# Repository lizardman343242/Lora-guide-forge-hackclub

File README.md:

# Lora-guide-forge-hackclub

This project follows the stranded guide from forge connecting the RP2040 to the Lora module leading into a antenna 

Bom Table
---
| Id | Designator | Footprint | Quantity | Designation | Supplier and ref |
|----|------------|-----------|----------|--------------|-------------------|
| 1 | AE1 | PinSocket_1x01_P2.54mm_Vertical | 1 | Antenna | |
| 2 | C2, C3 | C_0402_1005Metric | 2 | 100nf | https://jlcpcb.com/partdetail/1877-CL05B104KO5NNNC/C1525|
| 3 | C4 | C_0402_1005Metric | 1 | 470nF | https://jlcpcb.com/partdetail/48344-CL05A474KP5NNNC/C47339|
| 4 | C5, C6 | C_0402_1005Metric | 2 | 47pF | https://jlcpcb.com/partdetail/1919-0402CG470J500NT/C1567|
| 5 | C7 | C_0402_1005Metric | 1 | 1nf | https://jlcpcb.com/partdetail/1875-0402B102K500NT/C1523|
| 6 | C8 | C_0402_1005Metric | 1 | 39pF | https://jlcpcb.com/partdetail/1915-0402CG390J500NT/C1563|
| 7 | C9, C10 | C_0402_1005Metric | 2 | 3.3pf | https://jlcpcb.com/partdetail/1917-0402CG3R3C500NT/C1565|
| 8 | C11, C12, C13, C14, C15, C16, C17, C24, C27, C28 | C_0402_1005Metric | 10 | 100nF | https://jlcpcb.com/partdetail/1877-CL05B104KO5NNNC/C1525|
| 9 | C18, C29 | C_0402_1005Metric | 2 | 1uF | https://jlcpcb.com/partdetail/15107-CL05A105KP5NNNC/C14445|
| 10 | C22, C23 | C_0402_1005Metric | 2 | 15pF | https://jlcpcb.com/partdetail/1900-0402CG150J500NT/C1548|
| 11 | C25, C26 | C_0402_1005Metric | 2 | 10uf | https://jlcpcb.com/partdetail/16204-CL05A106MQ5NUNC/C15525|
| 12 | FB2 | L_0402_1005Metric | 1 | BLM15AX102SN1D | https://jlcpcb.com/partdetail/MurataElectronics-BLM15AX102SN1D/C85815|
| 13 | FL1 | Balun_Johanson_0900FM15K0039 | 1 | 0900FM15K0039 | https://jlcpcb.com/partdetail/JohansonDielectrics-0900FM15K0039E/C5224443|
| 14 | J1 | USB_C_Receptacle_GCT_USB4105-xx-A_16P_TopMnt_Horizontal | 1 | USB_C_Receptacle_USB2.0_16P | https://jlcpcb.com/partdetail/Korean_HropartsElec-TYPE_C_31_M12/C165948|
| 15 | L1 | L_0402_1005Metric | 1 | 15uH | |
| 16 | L2 | L_0402_1005Metric | 1 | 47nH | |
| 17 | L3 | L_0402_1005Metric | 1 | 9.1nH | |
| 18 | R1 | R_0402_1005Metric | 1 | 100 | |
| 19 | R2 | R_0402_1005Metric | 1 | 10k | |
| 20 | R3, R4 | R_0402_1005Metric | 2 | 27.4 | |
| 21 | R5, R6 | R_0402_1005Metric | 2 | 1K | |
| 22 | R7, R8 | R_0402_1005Metric | 2 | 5.1k | |
| 23 | SW1 | SW_Tactile_SPST_NO_Straight_CK_PTS636Sx25SMTRLFS | 1 | BOOT | |
| 24 | SW2 | SW_Tactile_SPST_NO_Straight_CK_PTS636Sx25SMTRLFS | 1 | RESET | |
| 25 | U1 | QFN-24-1EP_4x4mm_P0.5mm_EP2.6x2.6mm | 1 | SX1262IMLTRT | |
| 26 | U2 | QFN-56-1EP_7x7mm_P0.4mm_EP3.2x3.2mm | 1 | RP2040 | |
| 27 | U3 | SOT-363_SC-70-6 | 1 | PE4259 | |
| 28 | U4 | SOIC-8_5.3x5.3mm_P1.27mm | 1 | W25Q128JVS | |
| 29 | U5 | SOT-23-5 | 1 | AP2112K-3.3 | |
| 30 | Y1 | Crystal_SMD_3225-4Pin_3.2x2.5mm | 1 | 32MHz | |
| 31 | Y2 | Crystal_SMD_Abracon_ABM8G-4Pin_3.2x2.5mm | 1 | 12MHz | |
---

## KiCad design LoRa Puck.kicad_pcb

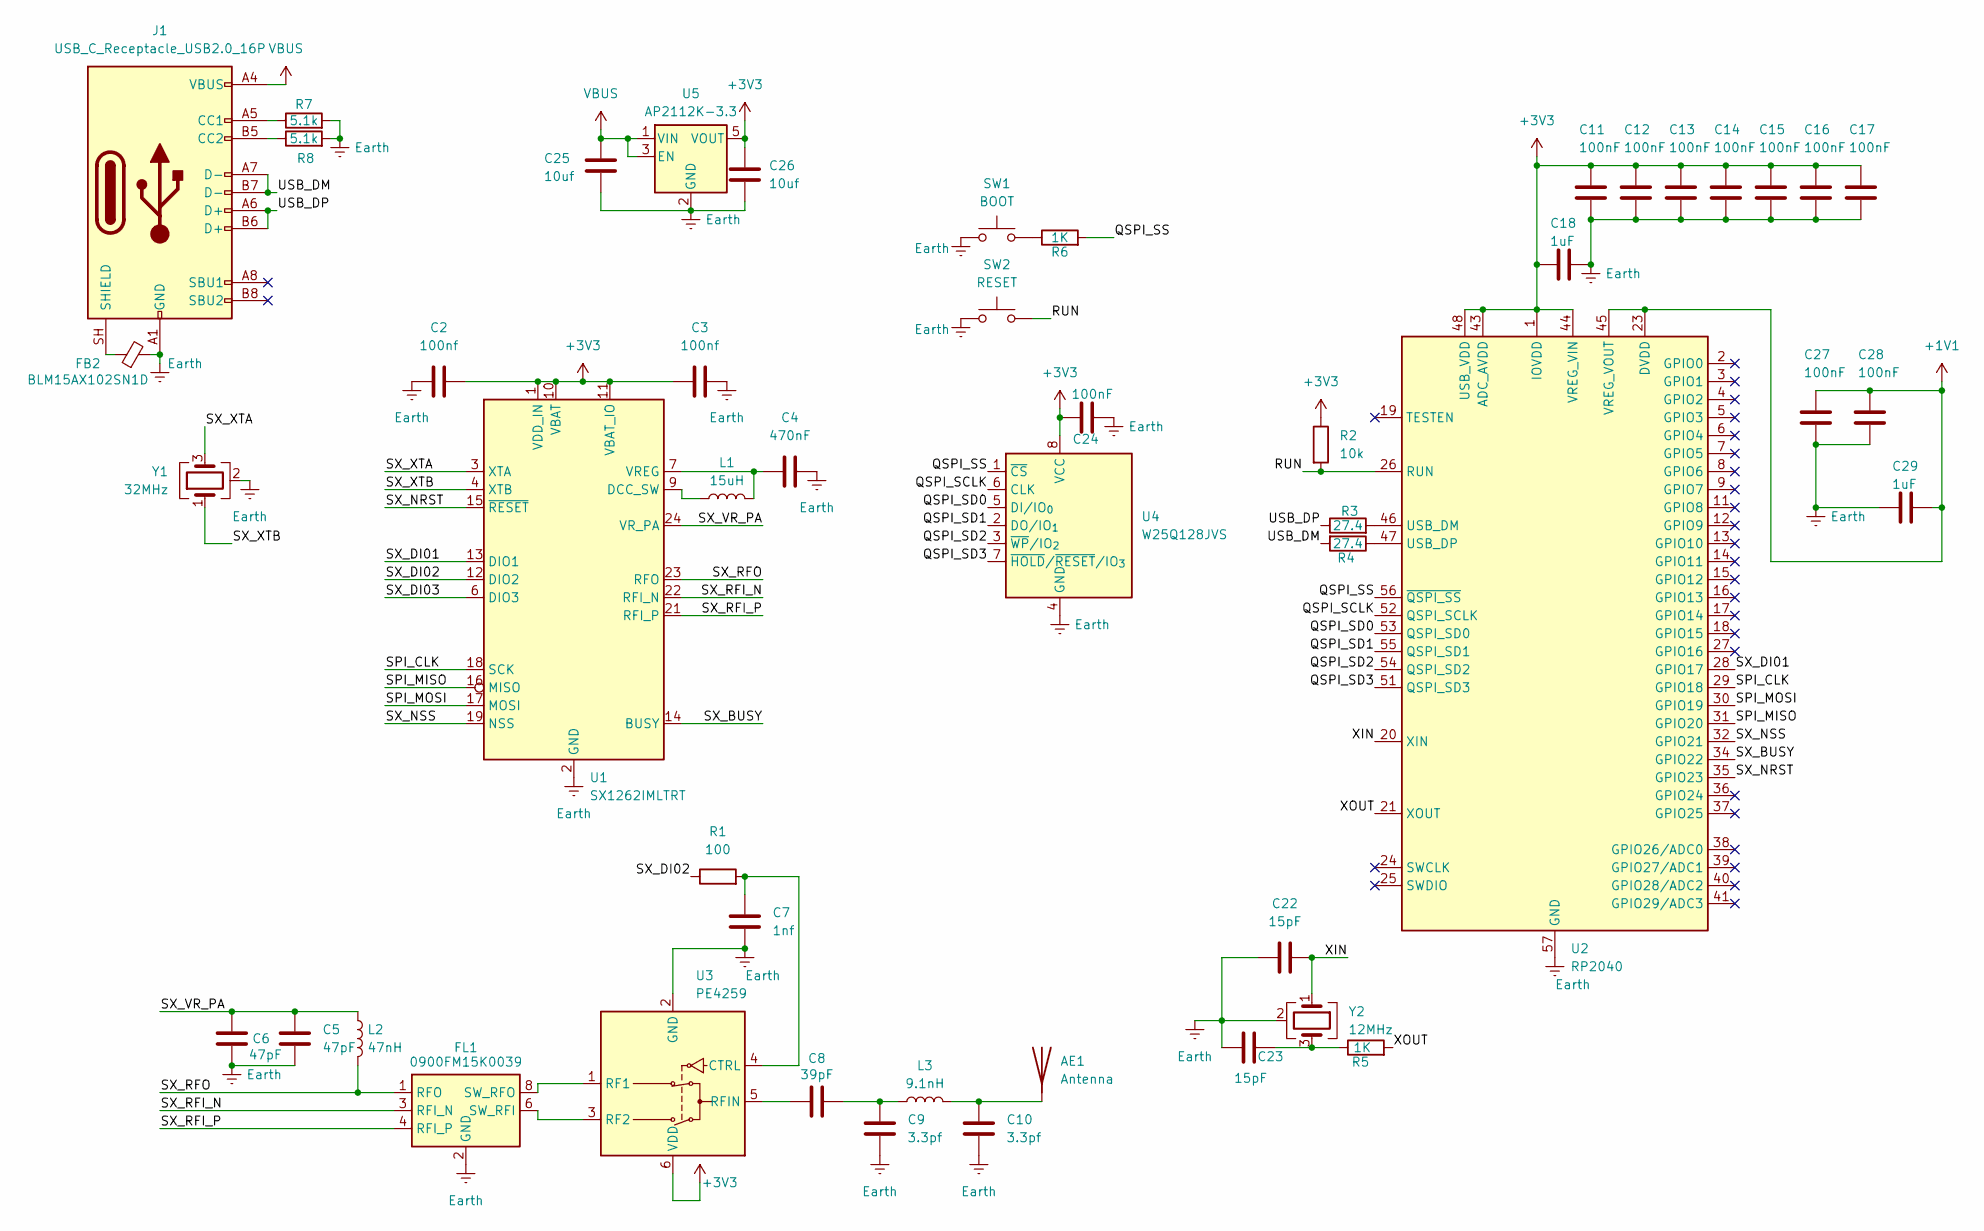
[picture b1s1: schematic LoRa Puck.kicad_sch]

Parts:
AE1: Antenna; PinSocket_1x01_P2.54mm_Vertical
C2, C3: 100nf; C_0402_1005Metric
C4: 470nF; C_0402_1005Metric
C5, C6: 47pF; C_0402_1005Metric
C7: 1nf; C_0402_1005Metric
C8: 39pF; C_0402_1005Metric
C9, C10: 3.3pf; C_0402_1005Metric
C11, C12, C13, C14, C15, C16, C17, C24, C27, C28: 100nF; C_0402_1005Metric
C18, C29: 1uF; C_0402_1005Metric
C22, C23: 15pF; C_0402_1005Metric
C25, C26: 10uf; C_0402_1005Metric
FB2: BLM15AX102SN1D; L_0402_1005Metric
FL1: 0900FM15K0039; Balun_Johanson_0900FM15K0039
J1: USB_C_Receptacle_USB2.0_16P; USB_C_Receptacle_GCT_USB4105-xx-A_16P_TopMnt_Horizontal
L1: 15uH; L_0402_1005Metric
L2: 47nH; L_0402_1005Metric
L3: 9.1nH; L_0402_1005Metric
R1: 100; R_0402_1005Metric
R2: 10k; R_0402_1005Metric
R3, R4: 27.4; R_0402_1005Metric
R5, R6: 1K; R_0402_1005Metric
R7, R8: 5.1k; R_0402_1005Metric
SW1: BOOT; SW_Tactile_SPST_NO_Straight_CK_PTS636Sx25SMTRLFS
SW2: RESET; SW_Tactile_SPST_NO_Straight_CK_PTS636Sx25SMTRLFS
U1: SX1262IMLTRT; QFN-24-1EP_4x4mm_P0.5mm_EP2.6x2.6mm
U2: RP2040; QFN-56-1EP_7x7mm_P0.4mm_EP3.2x3.2mm
U3: PE4259; SOT-363_SC-70-6
U4: W25Q128JVS; SOIC-8_5.3x5.3mm_P1.27mm
U5: AP2112K-3.3; SOT-23-5
Y1: 32MHz; Crystal_SMD_3225-4Pin_3.2x2.5mm
Y2: 12MHz; Crystal_SMD_Abracon_ABM8G-4Pin_3.2x2.5mm

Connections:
+1V1: C27.2, C28.2, C29.2, U2.23 (DVDD), U2.45 (VREG_VOUT), U2.50 (DVDD)
+3V3: C2.2, C3.1, C11.2, C12.2, C13.2, C14.2, C15.2, C16.2, C17.2, C18.1, C24.2, C26.1, R2.1, U1.1 (VDD_IN), U1.10 (VBAT), U1.11 (VBAT_IO), U2.1 (IOVDD), U2.10 (IOVDD), U2.22 (IOVDD), U2.33 (IOVDD), U2.42 (IOVDD), U2.43 (ADC_AVDD), U2.44 (VREG_VIN), U2.48 (USB_VDD), U2.49 (IOVDD), U3.6 (VDD), U4.8 (VCC), U5.5 (VOUT)
/QSPI_SCLK: U2.52 (QSPI_SCLK), U4.6 (CLK)
/QSPI_SD0: U2.53 (QSPI_SD0), U4.5 (DI/IO_{0})
/QSPI_SD1: U2.55 (QSPI_SD1), U4.2 (DO/IO_{1})
/QSPI_SD2: U2.54 (QSPI_SD2), U4.3 (~WP/IO_{2})
/QSPI_SD3: U2.51 (QSPI_SD3), U4.7 (~HOLD/~RESET/IO_{3})
/QSPI_SS: R6.2, U2.56 (~QSPI_SS), U4.1 (~CS)
/RUN: R2.2, SW2.2, U2.26 (RUN)
/SPI_CLK: U1.18 (SCK), U2.29 (GPIO18)
/SPI_MISO: U1.16 (MISO), U2.31 (GPIO20)
/SPI_MOSI: U1.17 (MOSI), U2.30 (GPIO19)
/SX_BUSY: U1.14 (BUSY), U2.34 (GPIO22)
/SX_DI01: U1.13 (DIO1), U2.28 (GPIO17)
/SX_DI02: R1.1, U1.12 (DIO2)
/SX_DI03: U1.6 (DIO3)
/SX_NRST: U1.15 (~RESET), U2.35 (GPIO23)
/SX_NSS: U1.19 (NSS), U2.32 (GPIO21)
/SX_RFI_N: FL1.3 (RFI_N), U1.22 (RFI_N)
/SX_RFI_P: FL1.4 (RFI_P), U1.21 (RFI_P)
/SX_RFO: FL1.1 (RFO), L2.2, U1.23 (RFO)
/SX_VR_PA: C5.2, C6.2, L2.1, U1.24 (VR_PA)
/SX_XTA: U1.3 (XTA), Y1.3
/SX_XTB: U1.4 (XTB), Y1.1
/USB_DM: J1.A7 (D-), J1.B7 (D-), R4.2
/USB_DP: J1.A6 (D+), J1.B6 (D+), R3.1
/XIN: C22.1, U2.20 (XIN), Y2.1
/XOUT: R5.2, U2.21 (XOUT)
Earth: C2.1, C3.2, C4.2, C5.1, C6.1, C7.2, C9.2, C10.2, C11.1, C12.1, C13.1, C14.1, C15.1, C16.1, C17.1, C18.2, C22.2, C23.2, C24.1, C25.2, C26.2, C27.1, C28.1, C29.1, FB2.2, FL1.2 (GND), FL1.5 (GND), FL1.7 (GND), FL1.9 (GND), FL1.10 (GND), J1.A1 (GND), J1.A12 (GND), J1.B1 (GND), J1.B12 (GND), R7.2, R8.2, SW1.1, SW2.1, U1.2 (GND), U1.5 (GND), U1.8 (GND), U1.20 (GND), U1.25 (GND), U2.57 (GND), U3.2 (GND), U4.4 (GND), U5.2 (GND), Y1.2 (G), Y1.4 (G), Y2.2 (G), Y2.4 (G)
unnamed: AE1.1 (A_1), C10.1, L3.2
unnamed: C8.2, C9.1, L3.1
unnamed: C23.1, R5.1, Y2.3
unnamed: FL1.6 (SW_RFI), U3.3 (RF2)
unnamed: FL1.8 (SW_RFO), U3.1 (RF1)
unnamed: J1.A5 (CC1), R7.1
unnamed: J1.B5 (CC2), R8.1
unnamed: FB2.1, J1.SH (SHIELD)
unnamed: R6.1, SW1.2
unnamed: L1.1, U1.9 (DCC_SW)
unnamed: C4.1, L1.2, U1.7 (VREG)
unnamed: R3.2, U2.46 (USB_DM)
unnamed: R4.1, U2.47 (USB_DP)
unnamed: C7.1, R1.2, U3.4 (CTRL)
unnamed: C8.1, U3.5 (RFIN)
VBUS: C25.1, J1.A4 (VBUS), J1.A9 (VBUS), J1.B4 (VBUS), J1.B9 (VBUS), U5.1 (VIN), U5.3 (EN)

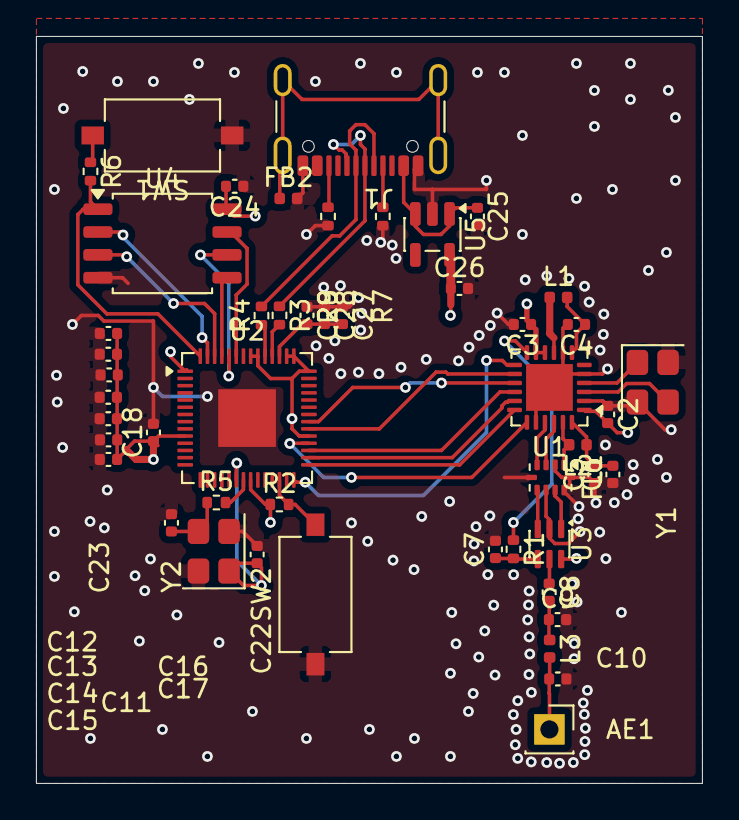
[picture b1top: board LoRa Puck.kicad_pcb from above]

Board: 4 copper layers, 37.0 x 41.5 mm, 49 parts (0 on the bottom side), 44 nets.
